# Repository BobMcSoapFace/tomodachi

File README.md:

# tomodachi

Tomodachi is a project to give you a heavily dependent and lazy panda to take care of, made because I need hardware and CAD design experience plus coding in firmware and also making panda themed gadgets is one of the coolest activities of all time

What the panda can do:
* Eat the food you give them (until they don't feel like it)
* Be head patted
* Perish

Features hand-drawn animations (more animations will come out once project is approed since I need the RTC to test more)

# materials

Name  | Quantity | Purchase link
------------- | ------------- | --------
ESP32C3  | 1 | [XIAO ESP32C3 DIP link](https://www.digikey.com/en/products/detail/seeed-technology-co-ltd/113991054/16652880)
DS3231 RTC | 1 | [DS3231 RTC link](https://www.ebay.com/itm/297741188722?chn=ps&google_free_listing_action=view_item)
Coin battery (for RTC if not included) | 1 | [Coin battery link](https://www.amazon.com/Murata-CR2032-Battery-Lithium-Coin/dp/B0B86LLWL8/ref=sr_1_2?crid=5N97OZSN6Z8H&dib=eyJ2IjoiMSJ9.F8PfWrmyizPbCG1gGso4Sn2BNfQ0eB1IYDHcMVNKymwzoMyjxj2rfjve1XwerShSBkc4a-dxVw_WuKlAkhaegxfFCFuhnR8R5kZjfYY0XphpTUnMTNZGNMzcZ4h64JS-bIkLakEKzOY6vGOThsG29ine8_IvoT9ieV70WUatbNnUaVEURMSSpseiIEaj0lkrKBS16BPGaSFWcJ-ryjQvp6fFocNM3I8KLXsGqz4SF25_1Fuxvltx6ggZdItXhQ_UIjJVnESPV-SKaemzGp7qIv84hWzi2OfmfkO0jIdj91Y.-Nvivpyu0MaXKH9qYVh21XHtwmFQd-MbeiVkGIs3xcA&dib_tag=se&keywords=cr2032+batteries&qid=1778205699&s=hpc&sprefix=CR2032+b%2Chpc%2C135&sr=1-2)
0.96in SSD1306 (128x64) | 1 | [SSD1306 (128x64)](https://www.aliexpress.us/item/3256807708805773.html?src=google&gatewayAdapt=glo2usa)
TP4056 | 1 | [TP4056 link](https://www.aliexpress.us/item/3256810410652428.html?src=google&gatewayAdapt=glo2usa)
Shottky diodes | 2 | this was the cheapest & most appropriate I could find -> [Schottky diodes link](https://www.amazon.com/VKLSVAN-15SQ045-Schottky-Diodes-Blocking/dp/B0DQGSDM6K/ref=sr_1_3?dib=eyJ2IjoiMSJ9.PRD4gvHdvDkC7SWHPaThgMwinM6Hy03ManybLbNwocMLrMJ9t_UkzCJYTdK0w7Lp_8ZR3MuXPNbKxz-Bt2SL9jdP8HabjVXBSTa6D2bg_bAsov6v16EMSgxGUxbWkNcjPib12Atslzx8aFsGQUOQaBg7FGf3G99chlaEFD5ZFAB9ur6NqzZEgtfETEsCHgCuqURKETHtwKPl8mpUCqiVJLfFYUm0_RdZWl7DTsZKh9o.iTZxRkUnYxQ1WVMXztBbVDkU00ySDiqvC2g8iIOHOFA&dib_tag=se&keywords=schottky+diode&qid=1778206254&refinements=p_85%3A2470955011&rnid=2470954011&rps=1&sr=8-3)
KY-040 Rotary Encoder | 1 | [KY-040 Rotary encoder link](https://www.aliexpress.us/item/3256810332864684.html?src=google&gatewayAdapt=glo2usa)
SS12F44 Switch | 1 | [SS12F44 Switch link](https://www.aliexpress.us/item/3256804709322450.html?src=google&gatewayAdapt=glo2usa)
Battery 18650 3.7V | 1 | [18650 battery link](https://www.digikey.com/en/products/detail/tinycircuits/ASR00050/9808766?gclsrc=aw.ds&gad_source=4&gad_campaignid=20243136172&gbraid=0AAAAADrbLlidfmJ5VH8HTIKUcIAKufJXb&gclid=CjwKCAjwtvvPBhBuEiwAPMijr8Klf8WiFOSPZoRulJW1RZkaHeSNISgGmuLmGddLyfp-fYC6PziE-xoCvMIQAvD_BwE)
Wires | |

(the material links were used assuming the fallout team has amazon prime for free shipping)

# design
## PCB Schematic

^note that the part labeled E1 is because Kicad was mad I have the SS12F44 switch connected by wires instead of traces, please ignore
## PCB Footprint

## Case

# assembly
steps:
1. 3d print the case, case cover and panda ears
   - PLA is going to be used in this project but recommended to use a more stronger & less brittle filament for snap fits
2. Flash the firmware by using Arduino IDE:
   1. Download the firmware folder and place the firmware folder inside a dedicated folder
   2. Unzip the libraries.zip and place "libraries" folder in the dedicated folder (named exactly that)
   3. Go to Arduino IDE File > Preferences and set the library folder to libraries
   4. Connect the XIAO ESP32C3 DIP to the computer with a USB-C cable, select the port that pops up and set the board as a "XIAO_ESP32C3"
   5. Go to "tomodachi_sketch.ino" and compile and upload
3. Solder the components to the PCB
   - Use header pins to connect the throughholes on both the pcb and components for easier soldering (though tinning the holes will work too)
   - Make sure to insert the coin battery into the RTC after soldering (heat damage might hurt the battery)
4. Solder a wire from the bottom left corner pad marked "CONNECT TO SWITCH" (<ins>not</ins> the throughholes connected to the D2 schottky diode) to one end of the SS12F44 switch's three pins, and then solder a wire from the Out+ of the TP4056 component (also marked with "CONNECT TO SWITCH") to the middle pin on the SS12F44 switch's three pins
   - The SS12F44 connects the middle pin with one or the other of the three pins depending on where it is switched
   - Use a short length wire when soldering the two places, and wrap each connection in electrical tape to ensure no short circuits happen
   - For both of the mentioned throughholes on the PCB probably don't use header pins as it will be easier to solder a wire without them
5. Place the battery in the case first, then solder the wire from the battery's + end to the TP4056's 5V hole, and the battery's - end to the TP4056's GND hole (both located on the edge of the PCB)
6. Assemble case with cover and ears

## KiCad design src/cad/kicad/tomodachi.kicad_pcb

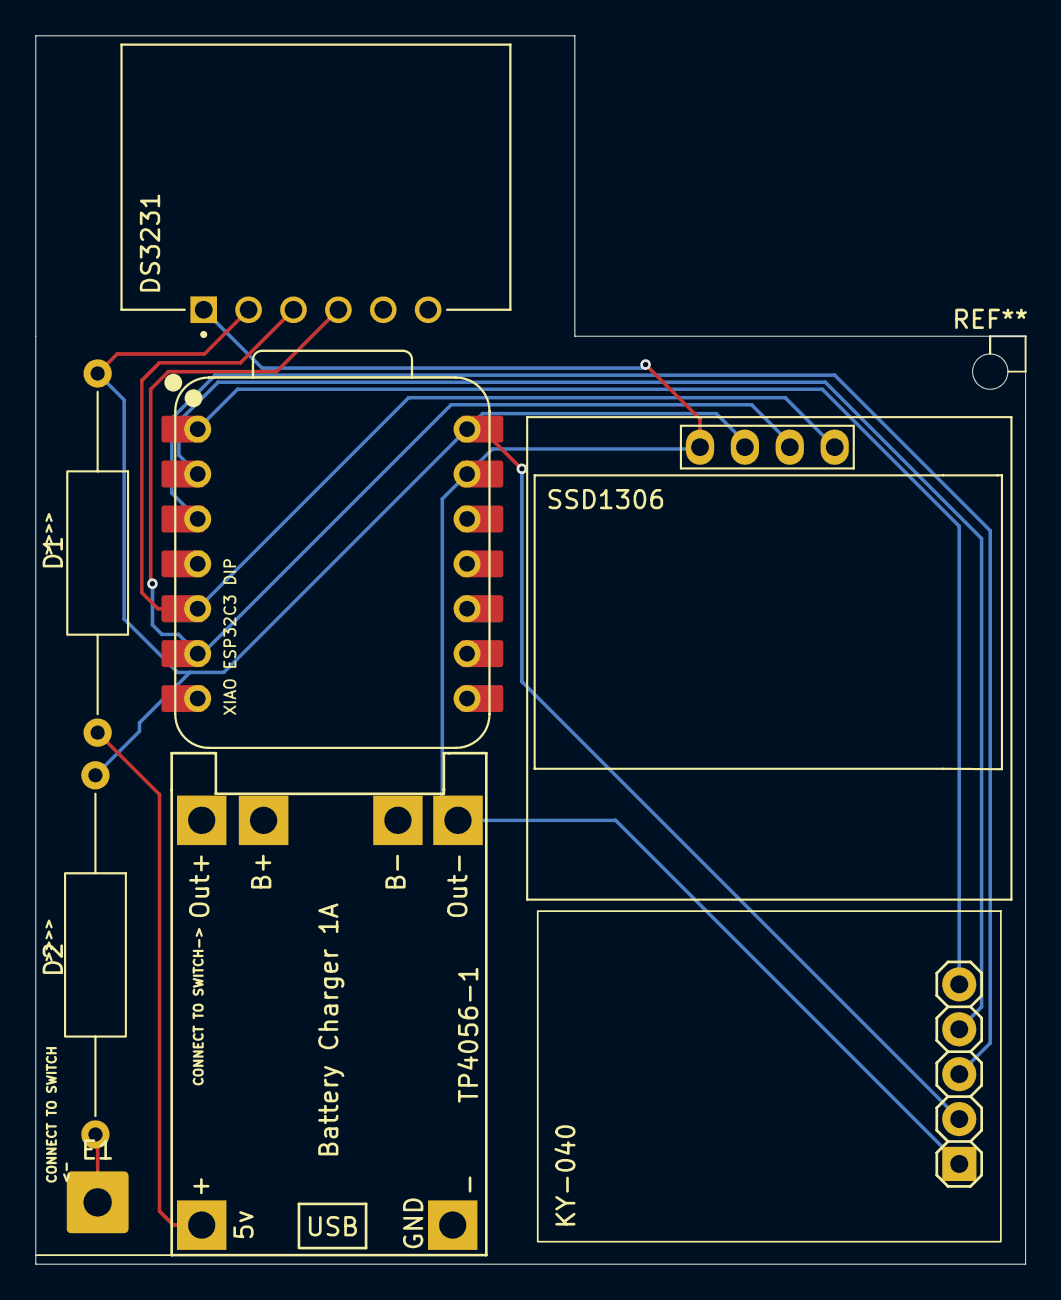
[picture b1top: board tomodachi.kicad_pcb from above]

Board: 2 copper layers, 56.0 x 69.5 mm, 8 parts (0 on the bottom side), 9 nets.

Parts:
D1, D2: D_Schottky; R_Axial_DIN0309_L9.0mm_D3.2mm_P20.32mm_Horizontal
DS3231: TC00500; MODULE_TC00500
E1: SolderWire-0.75sqmm_1x01_D1.25mm_OD3.5mm
KY-040: KY-040; KY-040-PORT
SSD1306: SSD1306128x64OLED
TP4056-1: TP4056-18650
XIAO ESP32C3 DIP: XIAO-ESP32-C3-DIP

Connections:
unnamed: D1.2 (A), TP4056-1.1 (5V)
unnamed: D1.1 (K), D2.1 (K), DS3231.5 (VCC), KY-040.VCC, SSD1306.2 (VCC), XIAO ESP32C3 DIP.14 (VBUS)
unnamed: D2.2 (A), E1.1
unnamed: DS3231.6 (GND), KY-040.GND, SSD1306.1 (GND), TP4056-1.4 (Out-), XIAO ESP32C3 DIP.13 (GND)
unnamed: DS3231.3 (SCL), SSD1306.3 (SCL), XIAO ESP32C3 DIP.6 (GPIO7_D5_SCL)
unnamed: DS3231.4 (SDA), SSD1306.4 (SDA), XIAO ESP32C3 DIP.5 (GPIO6_D4_SDA)
unnamed: KY-040.CLK, XIAO ESP32C3 DIP.1 (GPIO2_A0_D0)
unnamed: KY-040.DT, XIAO ESP32C3 DIP.2 (GPIO3_A1_D1)
unnamed: KY-040.SW, XIAO ESP32C3 DIP.3 (GPIO4_A2_D2)

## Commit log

2026-05-08 uploaded zine poster
2026-05-08 updated README on why I made this project (pandas)
2026-05-08 fixed README
2026-05-09 uploaded firmware & libraries
2026-05-09 added sketch source code
2026-05-09 fixed PCB & added BOM and 3D files
2026-05-09 updated README w/ instructions
2026-05-09 updated README w/ instructions about flashing
2026-05-09 updated BOM
2026-05-11 fixed missing zine and cad files
